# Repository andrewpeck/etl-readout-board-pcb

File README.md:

# Table of Contents <span class="tag" data-tag-name="TOC_4"><span class="smallcaps">TOC\_4</span></span>

  - [Useful Links](#useful-links)
      - [Relevant Presentations](#relevant-presentations)
  - [Block Diagrams](#block-diagrams)
      - [Data Flow](#data-flow)
      - [Power Distribution](#power-distribution)
      - [Control and Monitoring](#control-and-monitoring)
  - [Connectors/Interfaces](#connectorsinterfaces)
  - [Mechanical Outline](#mechanical-outline)
  - [Jumpers](#jumpers)
  - [Pin Assignments](#pin-assignments)
      - [E-Link Assignments](#e-link-assignments)
      - [LPGBT Pin Assignments](#lpgbt-pin-assignments)
      - [SCA Pin Assignments](#sca-pin-assignments)

## Useful Links

  - TDR -
    [LHCC-P-009](https://cds.cern.ch/record/2296612/files/LHCC-P-009.pdf)

### Relevant Presentations

  - 2019/05/13 - [Update on Power board and Patch
    Panel-0](https://indico.cern.ch/event/820512/contributions/3429658/attachments/1842929/3023621/ETL-Cabling-S_Los-May13-2019.pdf)
    (Sergey V.)
  - 2020/03/09 - [ETL LV powering
    scheme](https://indico.cern.ch/event/902328/contributions/3798257/attachments/2008611/3355343/2020-03-09_LV_scheme.pdf)
    (Natalia K.)
  - 2020/04/05 - [ETL Readout Board
    v2](https://indico.cern.ch/event/906805/contributions/3815774/attachments/2016073/3369701/2020-04-05-ETL-RBv2-Boston.pdf)
    (Andy P.)
  - 2020/04/27 - [EIE
    Dataformat](https://indico.cern.ch/event/912420/contributions/3837314/attachments/2026902/3391190/Andy_Liu_-_Emulator_v1.1.pdf)
    (Andy L.)
  - 2020/06/02 - [ETROC Power
    consumption](https://indico.cern.ch/event/931796/contributions/3915833/attachments/2061731/3458677/ETROC2-power-update-v1.pdf)
    (Andy P.)
  - 2020/07/13 - [Readout Board
    Interfaces](https://indico.cern.ch/event/939160/contributions/3946133/attachments/2073487/3481402/20200713_readout_board_interfaces.pdf)
    (Andy P.)
  - 2020/08/31 - [Readout Board v2
    Update](https://indico.cern.ch/event/950697/contributions/3993986/attachments/2093983/3519322/20200831_readout_board_v2.pptx.pdf)
    (Andy P.)
  - 2020/08/31 - [Power Board
    Status](https://indico.cern.ch/event/950697/contributions/3993988/attachments/2094005/3519146/ETL-PowerConversion-S_Los-Aug31-2020.pdf)
    (Sergey V.)

## Block Diagrams

### Data Flow

### Power Distribution

### Control and Monitoring

## Connectors/Interfaces

## Mechanical Outline

## Jumpers

## Pin Assignments

### E-Link Assignments

### LPGBT Pin Assignments

### SCA Pin Assignments

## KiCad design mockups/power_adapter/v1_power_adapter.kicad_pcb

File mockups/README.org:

* Adapters & Mockup Files
** Power adapter
- [[file:power_adapter/v1_power_adapter.pdf][Schematic]]
- [[file:power_adapter/gerber/v1_power_adapter_gerber_20200714.zip][v1_power_adapter_gerber_20200714.zip]]
#+attr_org: :width 300px
[[file:images/power_adapter.png]]
** Emulator Adapter
Adapter board to connect to the ETROC emulator.
- [[file:adapterv1.0.zip][adapterv1.0.zip]]
#+attr_org: :width 500px
[[file:images/adapter_both_sides.png]]
** [[file:ETL_RB_mock1v2.zip][ETL_RB_mock1v2.zip]]
Mockup of a 3 module readout board with realistic pad connectivity
#+attr_org: :width 600px
[[file:images/mock1v2.png]]
** [[file:ETL_RB_mock2v2.zip][ETL_RB_mock2v2.zip]]
Mockup of a 3 module readout board with daisy-chain connectivity
#+attr_org: :width 600px
[[file:images/mock2v2.png]]
** [[file:module_mockv3.zip][module_mockv3.zip]]
Mockup of a full-sized module (2 sensors, 4 etrocs) with daisy-chain connectivity
#+attr_org: :width 200px
[[file:images/module_mock.png]]
** [[file:ETL_BKv2.zip][ETL_BKv2.zip]]
Module-like breakout board
#+attr_org: :width 200px
[[file:images/module_breakout.png]]

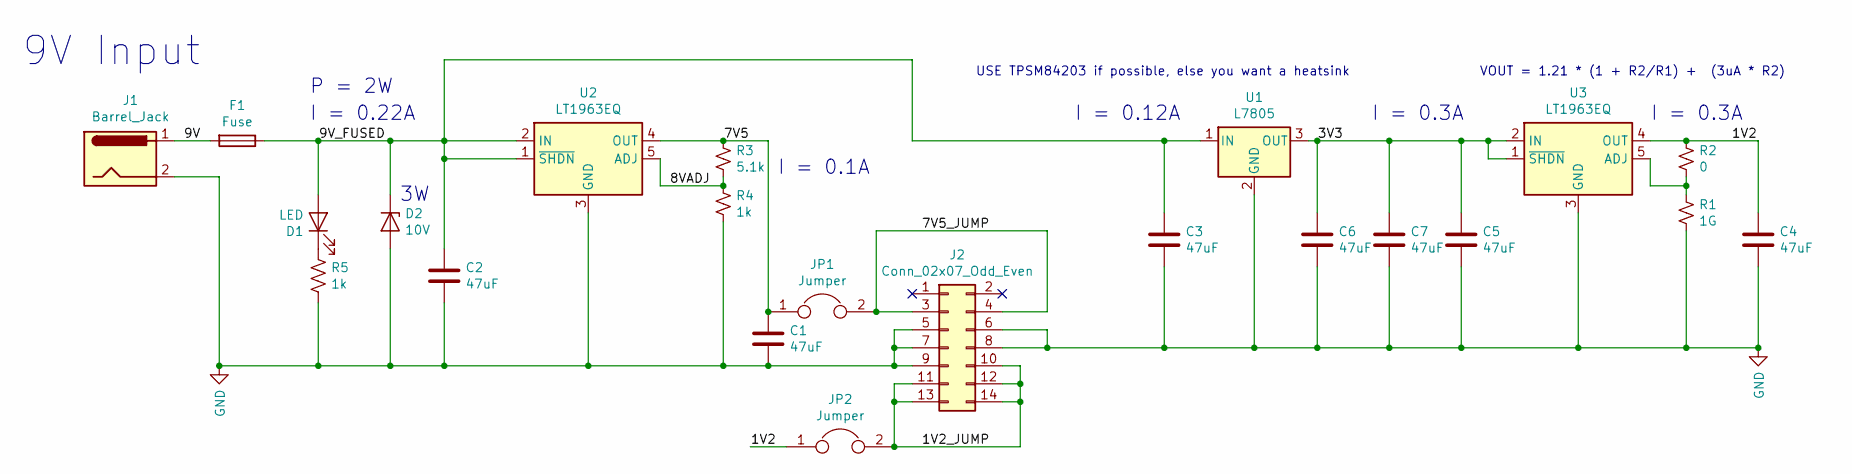
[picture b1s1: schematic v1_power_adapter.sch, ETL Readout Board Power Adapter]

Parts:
C1, C2, C3, C4, C5, C6, C7: 47uF; C_1210_3225Metric_Pad1.42x2.65mm_HandSolder
D1: LED; LED_0603_1608Metric_Pad1.05x0.95mm_HandSolder
D2: 10V; D_SMB_Handsoldering
F1: Fuse; Fuse_1206_3216Metric_Pad1.42x1.75mm_HandSolder
J1: Barrel_Jack; BarrelJack_CUI_PJ-063AH_Horizontal
J2: Conn_02x07_Odd_Even; PinSocket_2x07_P2.54mm_Vertical
JP1, JP2: Jumper; PinHeader_1x02_P2.54mm_Vertical
R1: 1G; R_0603_1608Metric_Pad1.05x0.95mm_HandSolder
R2: 0; R_0603_1608Metric_Pad1.05x0.95mm_HandSolder
R3: 5.1k; R_0603_1608Metric_Pad1.05x0.95mm_HandSolder
R4, R5: 1k; R_0603_1608Metric_Pad1.05x0.95mm_HandSolder
U1: L7805; TO-220-3_Vertical
U2, U3: LT1963EQ; TO-263-5_TabPin3

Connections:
/1V2: C4.1, JP2.1, R2.1, U3.4 (OUT)
/1V2_JUMP: J2.10, J2.11, J2.12, J2.13, J2.14, JP2.2
/3V3: C5.1, C6.1, C7.1, U1.3 (OUT), U3.1 (~SHDN), U3.2 (IN)
/7V5: C1.1, JP1.1, R3.1, U2.4 (OUT)
/7V5_JUMP: J2.3, J2.4, JP1.2
/8VADJ: R3.2, R4.1, U2.5 (ADJ)
/9V: F1.2, J1.1
/9V_FUSED: C2.1, C3.1, D1.2 (A), D2.1 (K), F1.1, U1.1 (IN), U2.1 (~SHDN), U2.2 (IN)
GND: C1.2, C2.2, C3.2, C4.2, C5.2, C6.2, C7.2, D2.2 (A), J1.2, J2.5, J2.6, J2.7, J2.8, J2.9, R1.2, R4.2, R5.2, U1.2 (GND), U2.3 (GND), U3.3 (GND)
unnamed: D1.1 (K), R5.1
unnamed: R1.1, R2.2, U3.5 (ADJ)

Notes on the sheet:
USE TPSM84203 if possible, else you want a heatsink
VOUT = 1.21 * (1 + R2/R1) + (3uA * R2)
9V Input
I = 0.3A
I = 0.1A
I = 0.12A
I = 0.22A
P = 2W

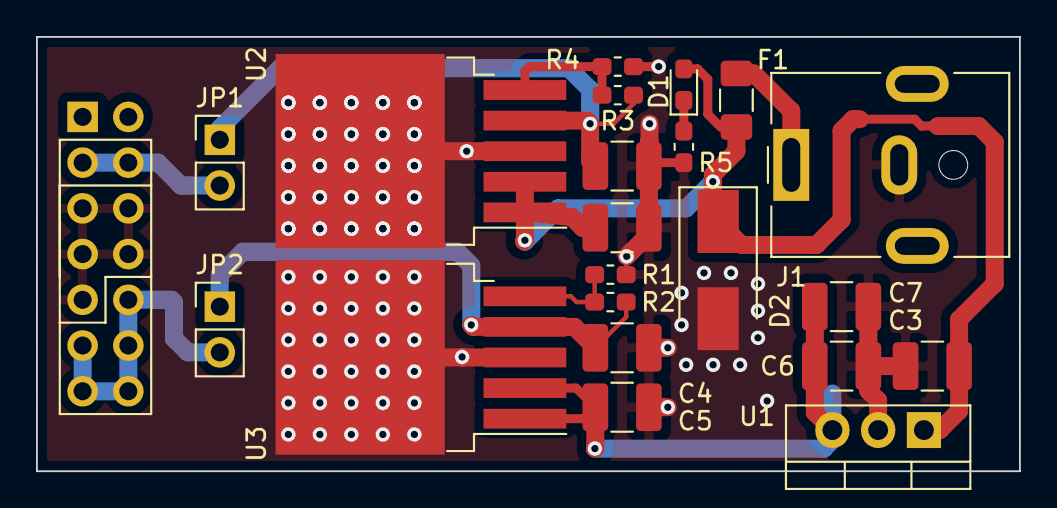
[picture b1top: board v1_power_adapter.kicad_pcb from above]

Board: 2 copper layers, 54.6 x 24.1 mm, 22 parts (1 on the bottom side), 11 nets.

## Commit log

2020-08-31 Resize images for gitlab...
2020-09-01 Add altium files
2020-09-01 Remove redundant readme
2020-09-03 Shrink images slightly, add gitignore
2020-09-03 Documentation & diagram updates
2020-09-03 Improve table formatting...
2020-09-03 Gitlab stinks :(
2020-09-03 Update module connectivity diagram
2020-09-04 Update diagram
2020-09-04 PCB updates from Mr. Wu
2020-09-04 Fix buggy drawio diagram
2020-09-04 Sort table in readme
2020-09-09 9/20/2020 version from Mr. Wu
2020-09-11 Updates from Mr. Wu
2020-09-11 Updates from 2020/09/11
    - Resistor values of voltage divider for ADC input reduced to keep impedance less than 1K
    - 1V2_RB input for ADC removed as lpGBT has internal channels for that already.
2020-09-11 Readme updates
2020-09-15 Add missing file
2020-09-24 Updates from 20200916
2020-10-26 Replace connectors with simple headers
2020-10-26 Update links in readme
2020-11-02 v1.6 Update from Mr. Wu
    - I just made some changes on the RB layout to make v1.6 It occurred to me that the current I2C bus has a problem that if one sensor module is bad, it can hold the all three modules dead.
    - This means we need eventually use GBT-SCA for I2C control.
    - So we need to make sure I2C masters of GBT-SCA is compatible with ETROC, so I changed two sensor modules I2C to GBT-SCA I2C masters.
    - I hope this is not going to change the quote as this is only a minor change.
    - Just want to let you know so that they don't start the production of v1.5 now.
2020-11-02 Update latest file pointers in README
2020-11-10 WP7B connectors' center groud strip width changed from 1mm to 0.8mm as recommended in its datasheet.
2020-11-19 Add mock-up files
2020-11-19 Test svg images
2020-11-19 Remove pngs
2020-11-24 Update BOM
2020-12-03 Add module breakout files
2020-12-03 Rename breakout zip file
2021-01-12 Update module mockups with correct spacing
2021-02-01 Add adapter board files
2021-02-01 Update mockup readme
2021-02-01 Combine top and bottom images
2021-03-03 Readme and diagram updates
2021-05-20 Add Andy's presentation
2021-05-20 Milestones
2021-05-20 Formatting
2021-05-20 Readme
2021-07-15 Add power adapter files
2021-07-15 Use grouped CSV
2021-07-15 Add jumpers for current measurement
2021-07-23 Fix project paths
2021-07-23 Move symbols to new ETL_RB.SCHLIB
2021-07-23 Aesthetic changes
2021-07-23 Moving LV/BV to new sheets
    Preparation for updating power design
2021-07-27 Component management
2021-08-03 Schematic & PCB maintainence
2021-08-03 Title block updates
2021-08-03 Split linpols to their own sheet; gang together linpol outputs
2021-08-03 LPGBT v1 changes
2021-08-03 WIP additions for external power
2021-08-04 "Refactoring" the schematic
2022-04-01 update title block
2022-04-01 cleanup organization
2022-04-04 connecting blocks, cleanup
2022-04-04 update title blocks and page numbers
2022-04-04 Refactor schematics
    - lpGBTs split into hierarchical blocks to reduce code duplication
    - additional work on connecting the top level
    - addition of an alternative LDO for the VTRX+
2022-04-04 Add documentation page link
    remove relevant presentations section
2022-04-04 add pigbt schematic
2022-04-04 Fix documentation page link
2022-05-05 renumber schematics
2022-05-31 more updates
    - add i2c mux
    - connect all clocks / elinks to harnesses
    - simplify board powering
    - misc cleanup
2022-06-01 cleanup, making connections
2022-06-02 annotate schematic
2022-07-26 Fix altium project
2022-07-26 create schematic library w/ all components
2022-07-29 updates toward v2
2022-08-31 Update analog monitoring / refactor schematics
2022-10-14 misc updates
2022-10-18 Schematic updates
2022-10-20 schematic / layout updates
2022-10-21 layout updates
2022-10-21 fix linpol12 enable
2022-10-21 remove the power connectors entirely, but add more GPIO to the connector for control
    per agreemtn with daniel and indara, we will move the power board
    connector to the breakout board to decouple from the pb design
2022-10-21 update outjob / renumber schematics
2022-10-25 replace sma with u.fl
2022-10-26 connect lv_rb to the module connector
2022-11-10 New version of ETL
2022-11-10 Re-commiting project
2022-11-11 updated project fixings errors
2022-11-14 update date / version in schematic
    also update outjob
2022-11-14 Add stackup files
2022-11-30 Fixing internal plane
2023-01-03 Add new emulator adapter design
2023-01-03 Add test stand baseplate files
2023-01-03 Add rb mockup files
2023-01-03 Add v3 RB mockup files
2023-01-03 Add date to emulator adapter pcb
2023-01-03 length matching for emulator board
2023-05-19 adding step file
2023-05-19 adding schematics PDF file
2023-05-19 modified outjob file
2023-06-12 Add footprint and schematic symbol for mux64
2023-06-14 updated SDA and SCL on RB connectors to be uniform
2023-06-14 Removed 1V5A and 1V4D test points, pull up resistors from SDA1/SDA2,and sca_led
2023-06-14 removed 1V5A and 1V4D voltage dividers
2023-06-14 removed 1V5 test point and linPOL12V which created 1V5A and 1V4D
2023-06-14 removed GBT-SCA that was powered by 1V5A and 1V4D
2023-06-14 saved doc
2023-06-14 updated MUX64 schematic symbol to better match current schematic colors
2023-06-14 replaces SCA with MUX64
2023-06-14 Added a note to last remaining SCA on page
2023-06-14 added power and ground to MUX64
2023-06-15 Save current project files
2023-06-15 moved testpoints
2023-06-15 craeted pdf of schematic
2023-06-20 saving pervious session comments
2023-06-20 Added select pins and removed SCA connected to master
2023-06-20 added Mod and WS reset
2023-06-20 Copied Linpol12 sheet to make powerboard connector
2023-06-20 Added Pgood and P_enable on servant gpio
2023-06-20 added PTAT signals as inputs to MUX64
2023-06-20 removed past pdf of schematic and created updated version
2023-06-20 updated project structure
2023-06-20 added voltage divider to MUX64 PTAT inputs
2023-06-20 Created pdf of current schematic
2023-06-22 removed SCA and renamed module digital and analog pins. Also reorganized MUX64 connections
2023-06-22 Annoted changed and created pdf
2023-06-22 format change
2023-06-22 added 1V2 PB monitoring channels to MUX64
2023-06-23 Added BV signals to MUX64
2023-06-23 Re-add outjob
2023-06-23 Update outjob
2023-06-23 added outjob and minor fixes to schematic
2023-06-23 remade schematic pdf and gerber files
2023-06-23 fixed minor errors
2023-06-23 renamed tag to Servant
2023-06-23 regenerated pdf and gerber files
2023-06-23 removed old pdf
2023-06-28 removed incorrect pdf schematic
